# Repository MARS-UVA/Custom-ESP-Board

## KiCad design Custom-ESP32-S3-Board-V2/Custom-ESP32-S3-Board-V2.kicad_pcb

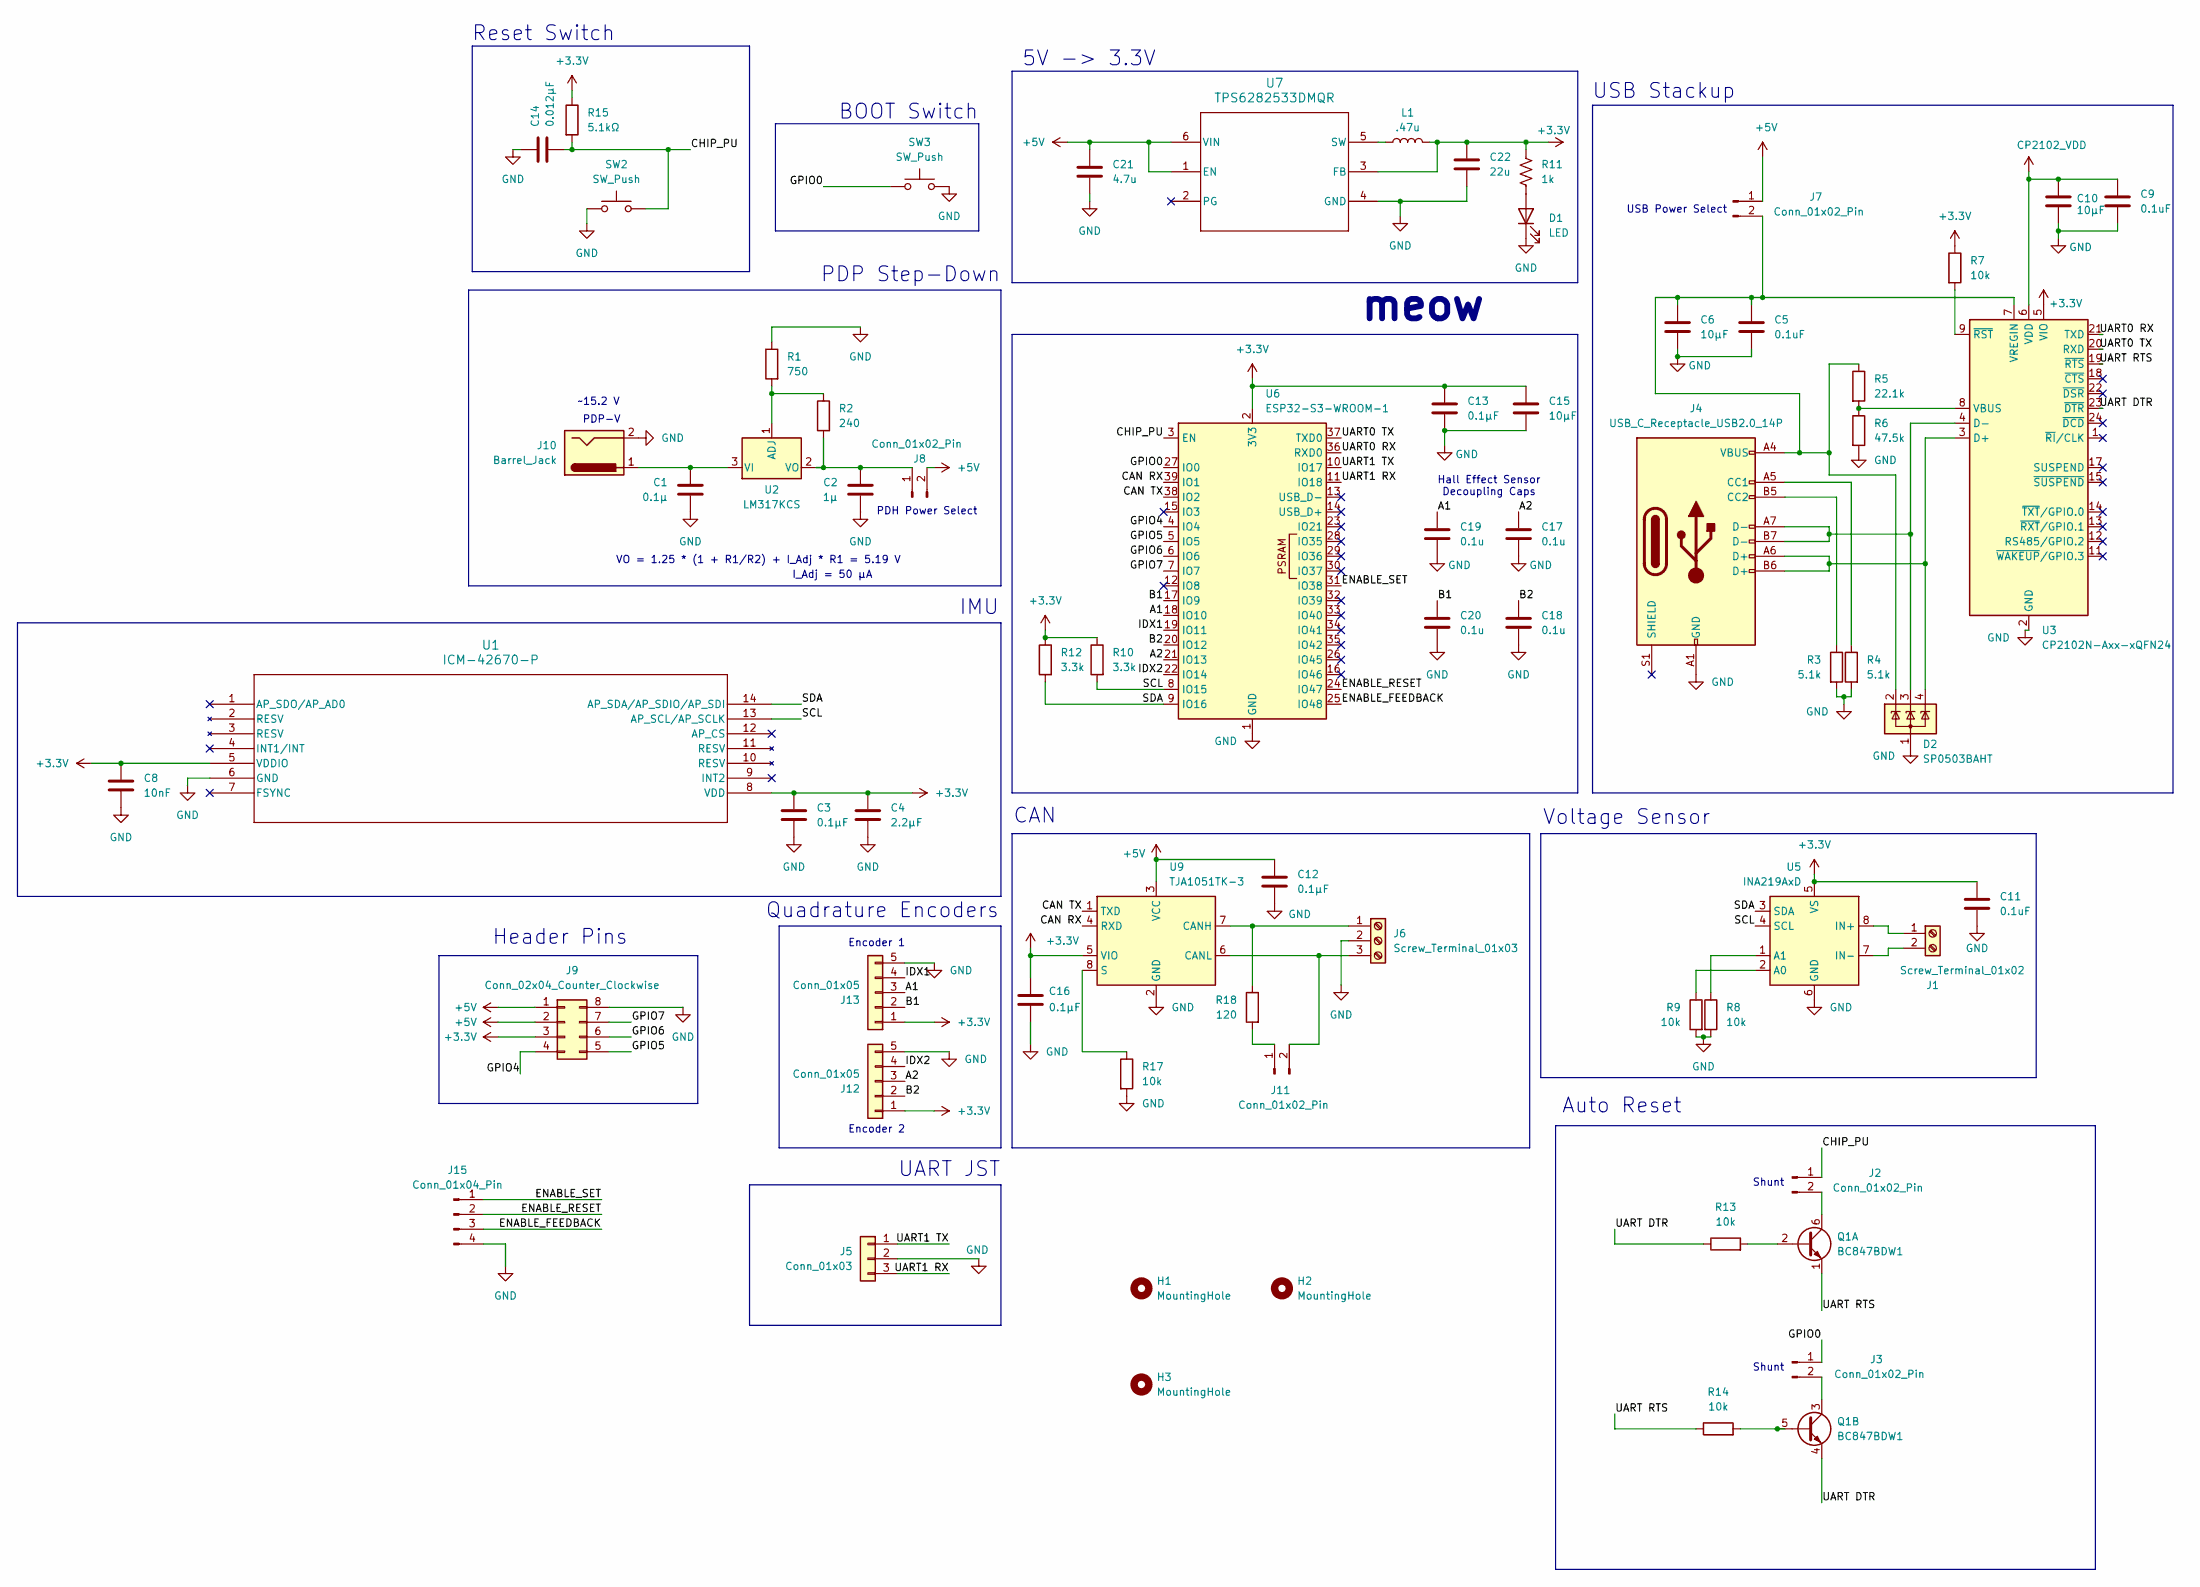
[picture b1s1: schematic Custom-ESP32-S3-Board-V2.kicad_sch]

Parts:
C1: 0.1µ; C_0402_1005Metric
C2: 1µ; C_0402_1005Metric
C3, C12, C13, C16: 0.1µF; C_0402_1005Metric
C4: 2.2µF; C_0402_1005Metric
C5, C9, C11: 0.1uF; C_0402_1005Metric
C6, C10, C15: 10µF; C_0402_1005Metric
C8: 10nF; C_0402_1005Metric
C14: 0.012µF; C_0402_1005Metric
C17, C18, C19, C20: 0.1u; C_0402_1005Metric
C21: 4.7u; C_0402_1005Metric
C22: 22u; C_0402_1005Metric
D1: LED; LED_0402_1005Metric
D2: SP0503BAHT; SOT-143
H1, H2, H3: MountingHole; MountingHole_4.5mm
J1: Screw_Terminal_01x02; TerminalBlock_Xinya_XY308-2.54-2P_1x02_P2.54mm_Horizontal
J2, J3, J7, J8, J11: Conn_01x02_Pin; PinHeader_1x02_P2.54mm_Vertical
J4: USB_C_Receptacle_USB2.0_14P; USB_C_Receptacle_HRO_TYPE-C-31-M-12
J5: Conn_01x03; JST_XH_S3B-XH-A-1_1x03_P2.50mm_Horizontal
J6: Screw_Terminal_01x03; TerminalBlock_Xinya_XY308-2.54-3P_1x03_P2.54mm_Horizontal
J9: Conn_02x04_Counter_Clockwise; PinHeader_2x04_P2.54mm_Vertical
J10: Barrel_Jack; BarrelJack_CUI_PJ-063AH_Horizontal
J12, J13: Conn_01x05; JST_XH_S5B-XH-A-1_1x05_P2.50mm_Horizontal
J15: Conn_01x04_Pin; JST_EH_B4B-EH-A_1x04_P2.50mm_Vertical
L1: .47u; L_0402_1005Metric
Q1: BC847BDW1; SOT-363_SC-70-6
R1: 750; R_0402_1005Metric
R2: 240; R_0402_1005Metric
R3, R4: 5.1k; R_0402_1005Metric
R5: 22.1k; R_0402_1005Metric
R6: 47.5k; R_0402_1005Metric
R7, R8, R9, R13, R14, R17: 10k; R_0402_1005Metric
R10, R12: 3.3k; R_0402_1005Metric
R11: 1k; R_0402_1005Metric
R15: 5.1kΩ; R_0402_1005Metric
R18: 120; R_0402_1005Metric
SW2, SW3: SW_Push; SW_SPST_PTS810
U1: ICM-42670-P; LGA14_2.5X3X0.76_IVS
U2: LM317KCS; TO-220-3_Vertical
U3: CP2102N-Axx-xQFN24; QFN-24-1EP_4x4mm_P0.5mm_EP2.6x2.6mm
U5: INA219AxD; SOIC-8_3.9x4.9mm_P1.27mm
U6: ESP32-S3-WROOM-1
U7: TPS6282533DMQR
U9: TJA1051TK-3; HVSON-8-1EP_3x3mm_P0.65mm_EP1.6x2.4mm

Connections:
+3.3V: C3.1, C4.1, C8.1, C11.1, C13.1, C15.1, C16.1, C22.1, J9.3, J12.1, J13.1, L1.2, R7.1, R10.1, R11.1, R12.1, R15.1, U1.5 (VDDIO), U1.8 (VDD), U3.5 (VIO), U5.5 (VS), U6.2 (3V3), U7.3 (FB), U9.5 (VIO)
+5V: C12.1, C21.1, J7.1, J8.2, J9.1, J9.2, U7.1 (EN), U7.6 (VIN), U9.3 (VCC)
/A1: C19.1, J13.3, U6.18 (IO10)
/A2: C17.1, J12.3, U6.21 (IO13)
/B1: C20.1, J13.2, U6.17 (IO9)
/B2: C18.1, J12.2, U6.20 (IO12)
/CAN RX: U6.39 (IO1), U9.4 (RXD)
/CAN TX: U6.38 (IO2), U9.1 (TXD)
/CHIP_PU: C14.2, J2.1, R15.2, SW2.2, U6.3 (EN)
/ENABLE_FEEDBACK: J15.3, U6.25 (IO48)
/ENABLE_RESET: J15.2, U6.24 (IO47)
/ENABLE_SET: J15.1, U6.31 (IO38)
/GPIO0: J3.1, SW3.2, U6.27 (IO0)
/GPIO4: J9.4, U6.4 (IO4)
/GPIO5: J9.5, U6.5 (IO5)
/GPIO6: J9.6, U6.6 (IO6)
/GPIO7: J9.7, U6.7 (IO7)
/IDX1: J13.4, U6.19 (IO11)
/IDX2: J12.4, U6.22 (IO14)
/SCL: R10.2, U1.13 (AP_SCL/AP_SCLK), U5.4 (SCL), U6.8 (IO15)
/SDA: R12.2, U1.14 (AP_SDA/AP_SDIO/AP_SDI), U5.3 (SDA), U6.9 (IO16)
/UART0 RX: U3.21 (TXD), U6.36 (RXD0)
/UART0 TX: U3.20 (RXD), U6.37 (TXD0)
/UART1 RX: J5.3, U6.11 (IO18)
/UART1 TX: J5.1, U6.10 (IO17)
/UART DTR: Q1.4 (E2), R13.1, U3.23 (~DTR)
/UART RTS: Q1.1 (E1), R14.1, U3.19 (~RTS)
CP2102_VDD: C9.1, C10.1, U3.6 (VDD)
GND: C1.2, C2.2, C3.2, C4.2, C5.2, C6.2, C8.2, C9.2, C10.2, C11.2, C12.2, C13.2, C14.1, C15.2, C16.2, C17.2, C18.2, C19.2, C20.2, C21.2, C22.2, D1.1 (K), D2.1 (A), J4.A1 (GND), J4.A12 (GND), J4.B1 (GND), J4.B12 (GND), J5.2, J6.2, J9.8, J10.2, J12.5, J13.5, J15.4, R1.1, R3.2, R4.2, R6.2, R8.2, R9.2, R17.2, SW2.1, SW3.1, U1.6 (GND), U3.2 (GND), U3.25 (GND), U5.6 (GND), U6.1 (GND), U6.40 (GND), U6.41 (GND), U7.4 (GND), U9.2 (GND), U9.9 (GND)
unnamed: D1.2 (A), R11.2
unnamed: J1.1, U5.8 (IN+)
unnamed: J1.2, U5.7 (IN-)
unnamed: J2.2, Q1.6 (C1)
unnamed: J3.2, Q1.3 (C2)
unnamed: J4.A5 (CC1), R4.1
unnamed: J4.B5 (CC2), R3.1
unnamed: J6.1, R18.1, U9.7 (CANH)
unnamed: C5.1, C6.1, D2.2 (K), J4.A4 (VBUS), J4.A9 (VBUS), J4.B4 (VBUS), J4.B9 (VBUS), J7.2, R5.1, U3.7 (VREGIN)
unnamed: C2.1, J8.1, R2.2, U2.2 (VO)
unnamed: J11.1, R18.2
unnamed: J6.3, J11.2, U9.6 (CANL)
unnamed: Q1.2 (B1), R13.2
unnamed: Q1.5 (B2), R14.2
unnamed: R1.2, R2.1, U2.1 (ADJ)
unnamed: C1.1, J10.1, U2.3 (VI)
unnamed: D2.4 (K), J4.A6 (D+), J4.B6 (D+), U3.3 (D+)
unnamed: D2.3 (K), J4.A7 (D-), J4.B7 (D-), U3.4 (D-)
unnamed: R5.2, R6.1, U3.8 (VBUS)
unnamed: R7.2, U3.9 (~RST)
unnamed: R9.1, U5.2 (A0)
unnamed: R8.1, U5.1 (A1)
unnamed: L1.1, U7.5 (SW)
unnamed: R17.1, U9.8 (S)

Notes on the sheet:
Encoder 1
VO = 1.25 * (1 + R1/R2) + I_Adj * R1 = 5.19 V
5V -> 3.3V
Reset Switch
Shunt
UART JST
Encoder 2
Quadrature Encoders
~15.2 V
USB Power Select
IMU
I_Adj = 50 µA
Auto Reset
Hall Effect Sensor Decoupling Caps
meow
CAN
PDP-V
Header Pins
PDH Power Select
BOOT Switch
USB Stackup
Voltage Sensor
PDP Step-Down

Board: 4 copper layers, 68 parts (0 on the bottom side), 53 nets, no tracks yet.

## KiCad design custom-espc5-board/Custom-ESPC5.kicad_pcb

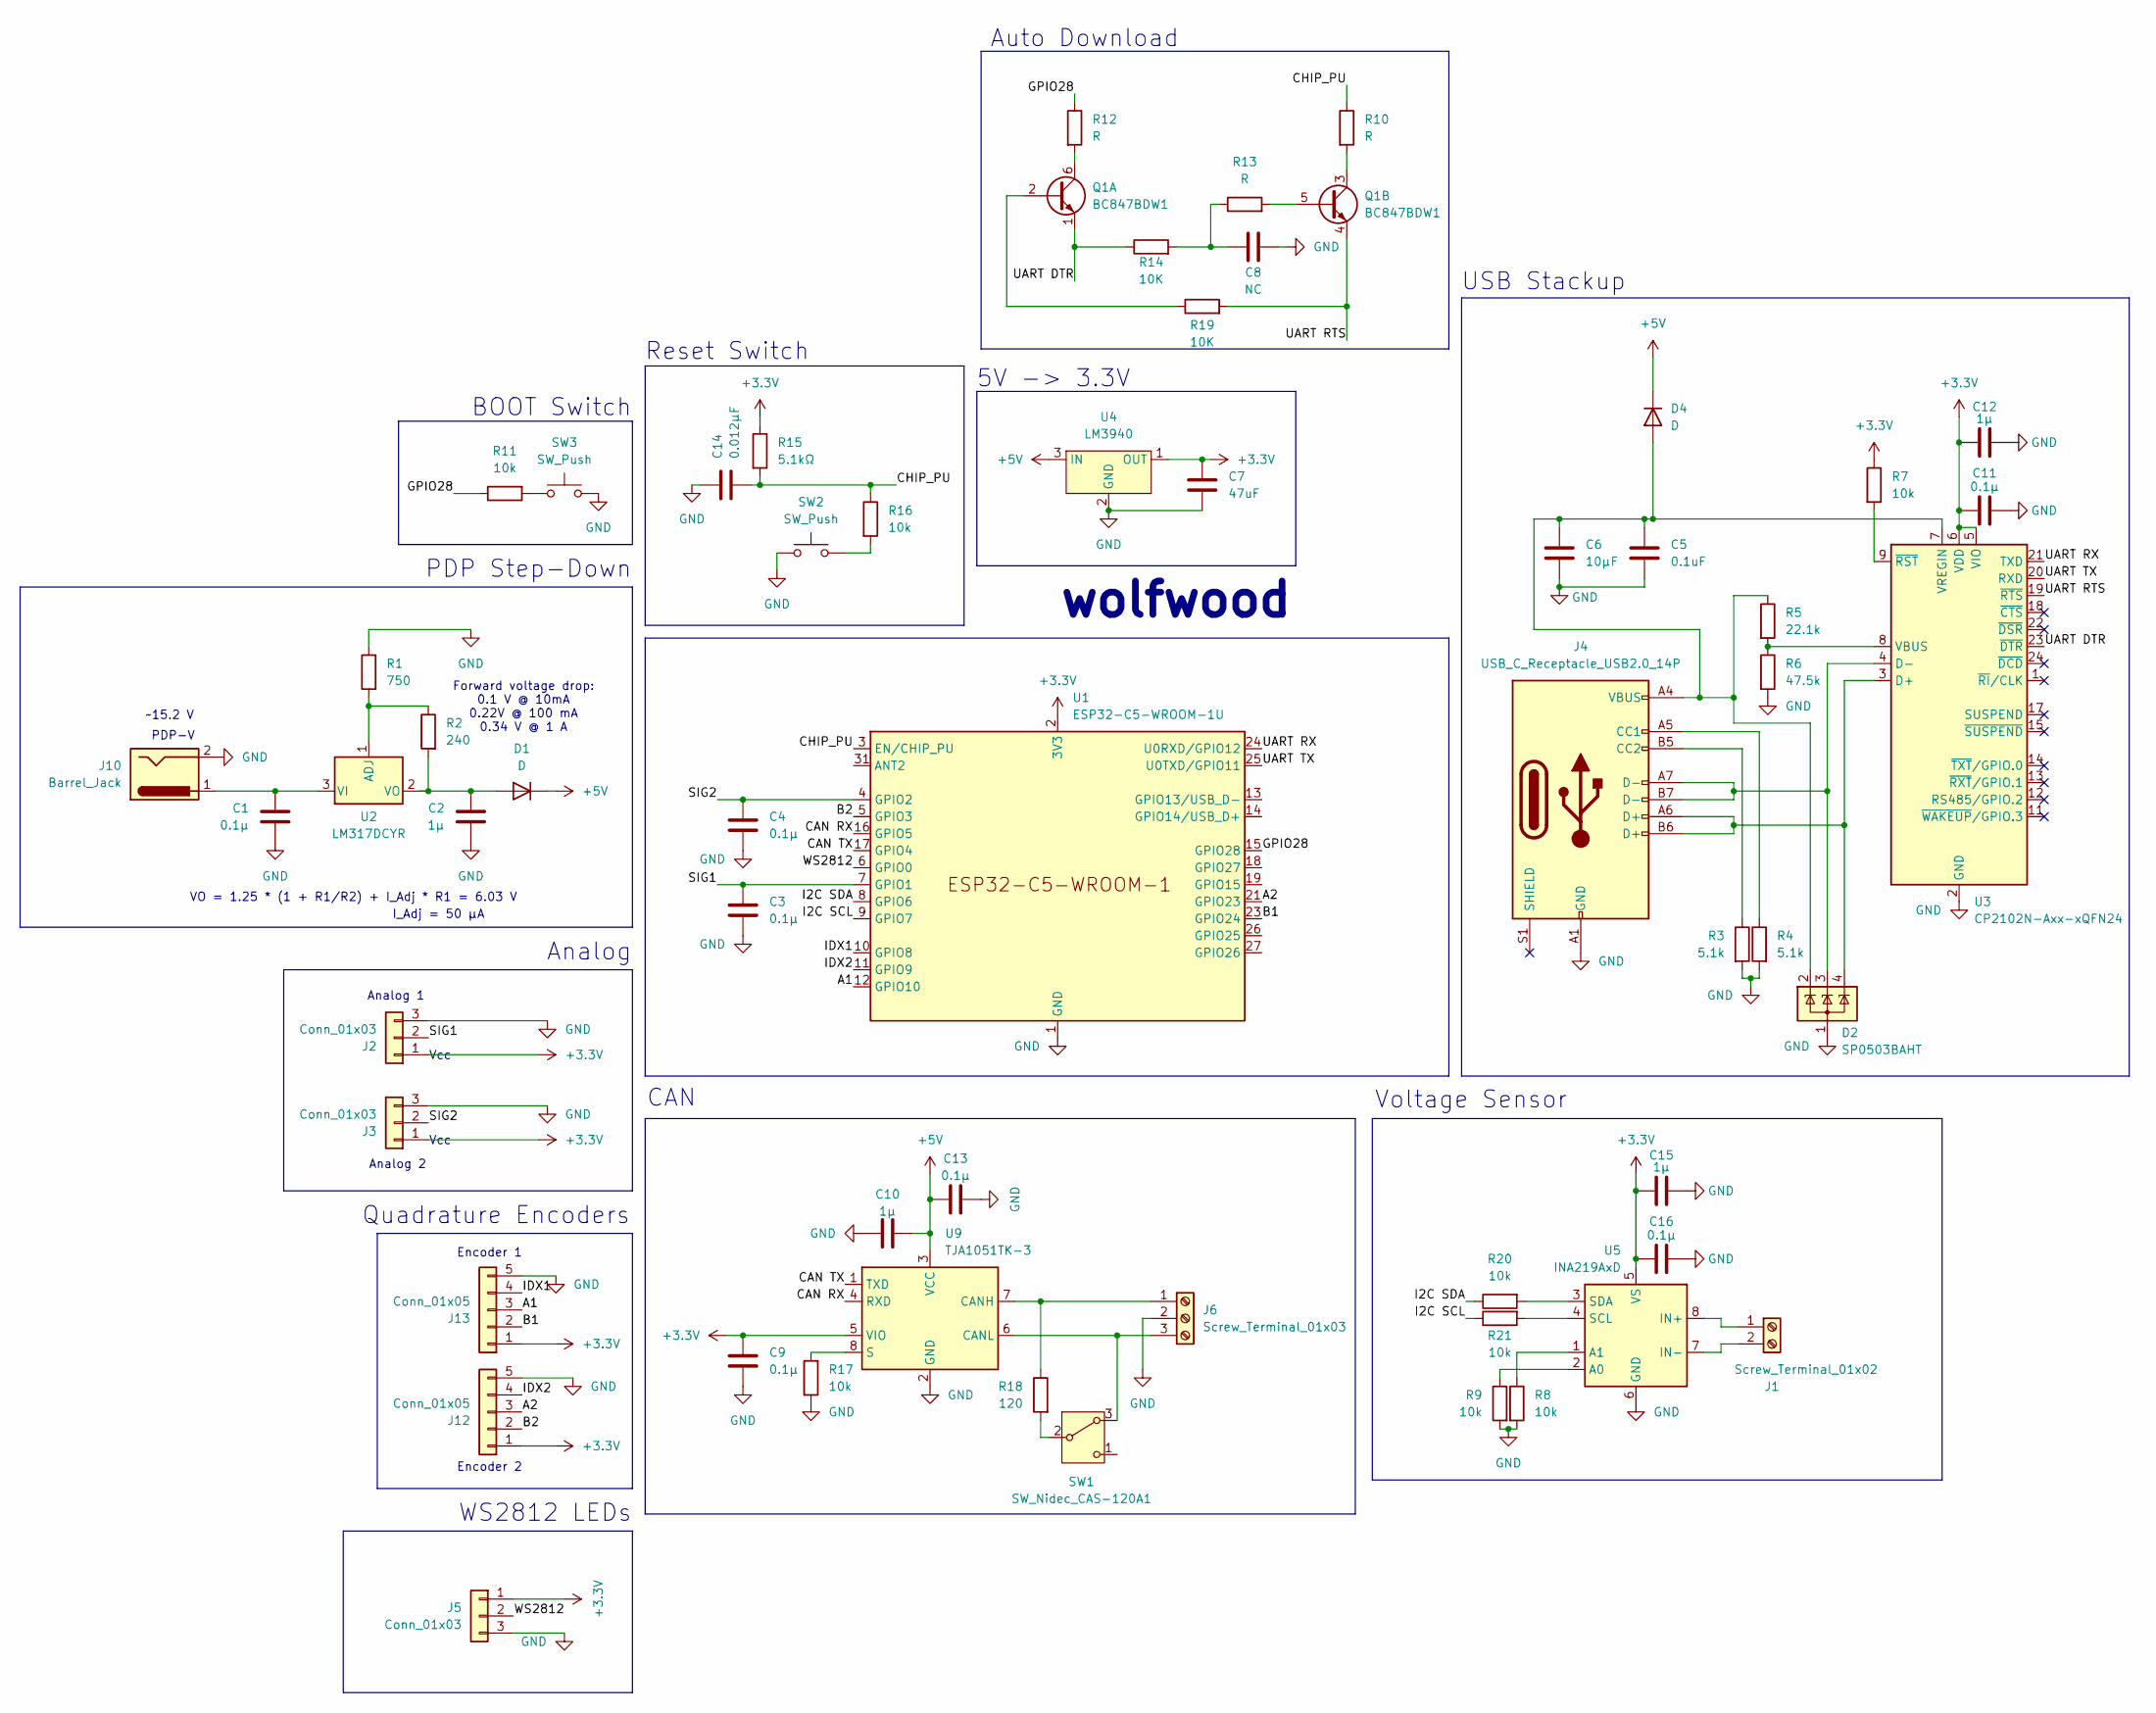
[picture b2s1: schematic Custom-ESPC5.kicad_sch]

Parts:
C1, C3, C4, C9, C11, C13, C16: 0.1µ; C_0402_1005Metric
C2, C10, C12, C15: 1µ; C_0402_1005Metric
C5: 0.1uF; C_0402_1005Metric
C6: 10µF; C_0402_1005Metric
C7: 47uF; C_0402_1005Metric
C8: NC; C_0402_1005Metric
C14: 0.012µF; C_0402_1005Metric
D1, D4: D; USC-TOS
D2: SP0503BAHT; SOT-143
J1: Screw_Terminal_01x02; TerminalBlock_Xinya_XY308-2.54-2P_1x02_P2.54mm_Horizontal
J2, J3, J5: Conn_01x03; JST_XH_S3B-XH-A-1_1x03_P2.50mm_Horizontal
J4: USB_C_Receptacle_USB2.0_14P; USB_C_Receptacle_HRO_TYPE-C-31-M-12
J6: Screw_Terminal_01x03; TerminalBlock_Xinya_XY308-2.54-3P_1x03_P2.54mm_Horizontal
J10: Barrel_Jack; BarrelJack_CUI_PJ-063AH_Horizontal
J12, J13: Conn_01x05; JST_XH_S5B-XH-A-1_1x05_P2.50mm_Horizontal
Q1: BC847BDW1; SOT-363_SC-70-6
R1: 750; R_0402_1005Metric
R2: 240; R_0402_1005Metric
R3, R4: 5.1k; R_0402_1005Metric
R5: 22.1k; R_0402_1005Metric
R6: 47.5k; R_0402_1005Metric
R7, R8, R9, R11, R16, R17, R20, R21: 10k; R_0402_1005Metric
R10, R12, R13: R; R_0402_1005Metric
R14, R19: 10K; R_0402_1005Metric
R15: 5.1kΩ; R_0402_1005Metric
R18: 120; R_0402_1005Metric
SW1: SW_Nidec_CAS-120A1; Nidec_Copal_CAS-120A
SW2, SW3: SW_Push; SW_SPST_PTS810
U1: ESP32-C5-WROOM-1U
U2: LM317DCYR; SOT-223-3_TabPin2
U3: CP2102N-Axx-xQFN24; QFN-24-1EP_4x4mm_P0.5mm_EP2.6x2.6mm
U4: LM3940; SOT-223-3_TabPin2
U5: INA219AxD; SOIC-8_3.9x4.9mm_P1.27mm
U9: TJA1051TK-3; HVSON-8-1EP_3x3mm_P0.65mm_EP1.6x2.4mm

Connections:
+3.3V: C7.1, C9.2, C11.2, C12.2, C15.2, C16.2, J2.1, J3.1, J5.1, J12.1, J13.1, R7.1, R15.1, U1.2 (3V3), U3.5 (VIO), U3.6 (VDD), U4.1 (OUT), U5.5 (VS), U9.5 (VIO)
+5V: C10.2, C13.2, D1.1 (K), D4.1 (K), U4.3 (IN), U9.3 (VCC)
/A1: J13.3, U1.12 (GPIO10)
/A2: J12.3, U1.21 (GPIO23)
/B1: J13.2, U1.23 (GPIO24)
/B2: J12.2, U1.5 (GPIO3)
/CAN RX: U1.16 (GPIO5), U9.4 (RXD)
/CAN TX: U1.17 (GPIO4), U9.1 (TXD)
/CHIP_PU: C14.2, R10.1, R15.2, R16.1, U1.3 (EN/CHIP_PU)
/GPIO28: R11.1, R12.1, U1.15 (GPIO28)
/I2C SCL: R21.1, U1.9 (GPIO7)
/I2C SDA: R20.1, U1.8 (GPIO6)
/IDX1: J13.4, U1.10 (GPIO8)
/IDX2: J12.4, U1.11 (GPIO9)
/SIG1: C3.1, J2.2, U1.7 (GPIO1)
/SIG2: C4.1, J3.2, U1.4 (GPIO2)
/UART DTR: Q1.1 (E1), R14.1, U3.23 (~DTR)
/UART RTS: Q1.4 (E2), R19.2, U3.19 (~RTS)
/UART RX: U1.24 (U0RXD/GPIO12), U3.21 (TXD)
/UART TX: U1.25 (U0TXD/GPIO11), U3.20 (RXD)
/WS2812: J5.2, U1.6 (GPIO0)
GND: C1.2, C2.2, C3.2, C4.2, C5.2, C6.2, C7.2, C8.2, C9.1, C10.1, C11.1, C12.1, C13.1, C14.1, C15.1, C16.1, D2.1 (A), J2.3, J3.3, J4.A1 (GND), J4.A12 (GND), J4.B1 (GND), J4.B12 (GND), J5.3, J6.2, J10.2, J12.5, J13.5, R1.1, R3.2, R4.2, R6.2, R8.2, R9.2, R17.2, SW2.1, SW3.1, U1.1 (GND), U1.28 (GND), U1.29 (GND), U1.30 (GND), U1.32 (GND), U3.2 (GND), U3.25 (GND), U4.2 (GND), U5.6 (GND), U9.2 (GND), U9.9 (GND)
unnamed: C8.1, R13.1, R14.2
unnamed: C2.1, D1.2 (A), R2.2, U2.2 (VO)
unnamed: C5.1, C6.1, D2.2 (K), D4.2 (A), J4.A4 (VBUS), J4.A9 (VBUS), J4.B4 (VBUS), J4.B9 (VBUS), R5.1, U3.7 (VREGIN)
unnamed: J1.1, U5.8 (IN+)
unnamed: J1.2, U5.7 (IN-)
unnamed: J4.A5 (CC1), R4.1
unnamed: J4.B5 (CC2), R3.1
unnamed: J6.1, R18.1, U9.7 (CANH)
unnamed: J6.3, SW1.3 (A), U9.6 (CANL)
unnamed: Q1.2 (B1), R19.1
unnamed: Q1.6 (C1), R12.2
unnamed: Q1.5 (B2), R13.2
unnamed: Q1.3 (C2), R10.2
unnamed: R11.2, SW3.2
unnamed: R16.2, SW2.2
unnamed: R18.2, SW1.2 (B)
unnamed: R1.2, R2.1, U2.1 (ADJ)
unnamed: C1.1, J10.1, U2.3 (VI)
unnamed: D2.4 (K), J4.A6 (D+), J4.B6 (D+), U3.3 (D+)
unnamed: D2.3 (K), J4.A7 (D-), J4.B7 (D-), U3.4 (D-)
unnamed: R5.2, R6.1, U3.8 (VBUS)
unnamed: R7.2, U3.9 (~RST)
unnamed: R9.1, U5.2 (A0)
unnamed: R8.1, U5.1 (A1)
unnamed: R21.2, U5.4 (SCL)
unnamed: R20.2, U5.3 (SDA)
unnamed: R17.1, U9.8 (S)

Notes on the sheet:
Quadrature Encoders
Encoder 1
USB Stackup
WS2812 LEDs
CAN
Auto Download
BOOT Switch
VO = 1.25 * (1 + R1/R2) + I_Adj * R1 = 6.03 V
Forward voltage drop: 0.1 V @ 10mA 0.22V @ 100 mA 0.34 V @ 1 A
Vcc
Analog
I_Adj = 50 µA
Analog 1
Reset Switch
PDP Step-Down
Voltage Sensor
~15.2 V
wolfwood
Analog 2
Encoder 2
PDP-V
5V -> 3.3V

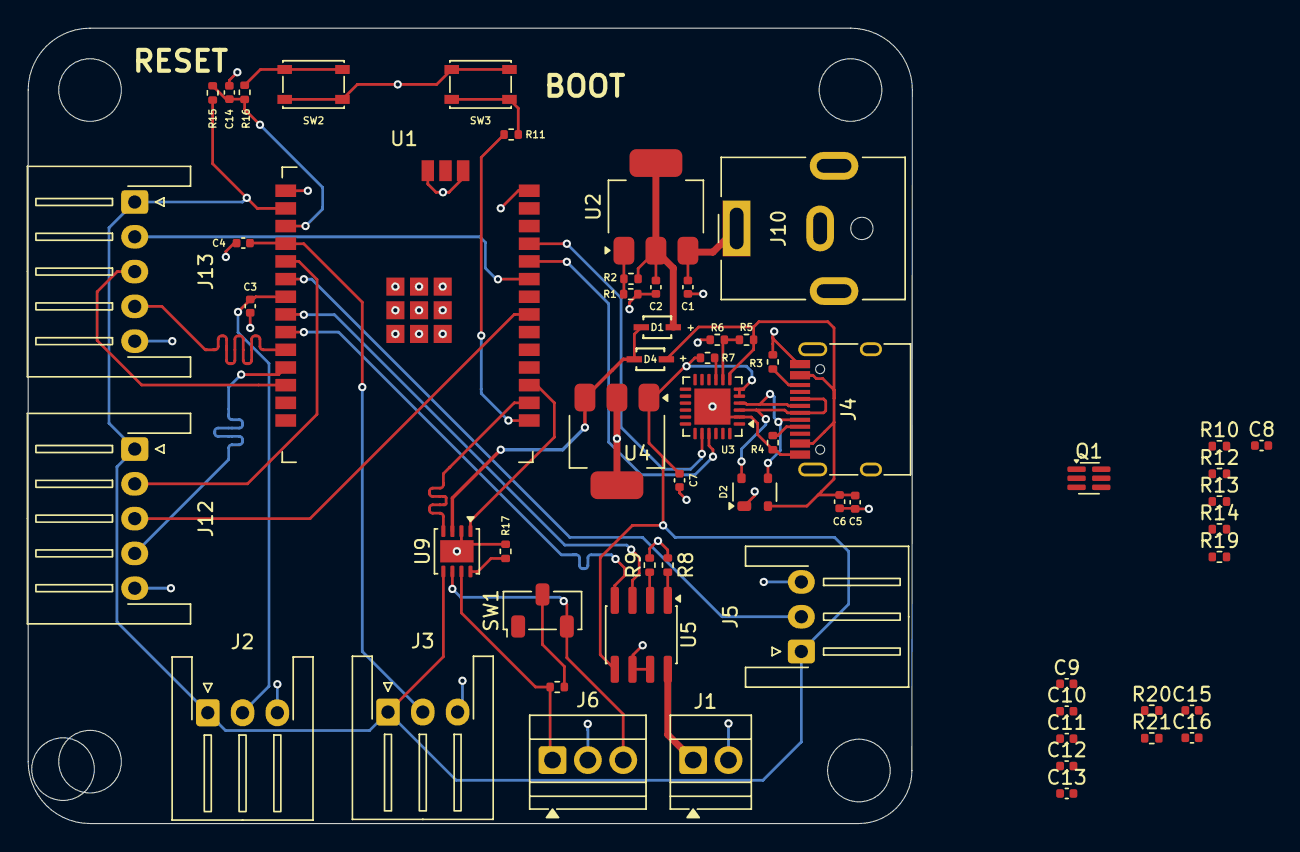
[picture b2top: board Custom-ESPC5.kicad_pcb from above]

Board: 4 copper layers, 63.5 x 57.1 mm, 59 parts (0 on the bottom side), 49 nets.

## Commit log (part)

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2026-02-20 Create blank project
2026-02-22 finish schem, start board work
2026-02-22 closed kicad
2026-02-22 aa
    fitting things into board dimensions
2026-02-23 board layout
2026-02-23 Finish preliminary board tracings (NOT COMPLETE)
2026-02-24 finish base
2026-02-24 custom board preliminary complete
2026-02-24 Increase density
2026-02-24 fix name
2026-03-11 fix some silkscreens, get rounded corners
2026-03-11 Update Custom-ESPC5.kicad_sch
    Made correction to lm317 circuit annotations
2026-03-12 Update Custom-ESPC5.kicad_sch
    Added datasheet link
2026-03-13 fixed schematic changes
    fixed schematic changes like master austin said
2026-03-15 Fix layout file formatting
2026-03-15 Update schematic
    Fix I2C pull-up resistors
2026-04-03 s3 devboard + imu
    austin yun
2026-04-05 Add bypass caps
2026-04-05 Changed voltage regulator footprints and schematic
2026-04-10 renamed folders
2026-04-10 Update layout
    apply schematic changes to layout
2026-04-17 add auto-reset
2026-04-17 Finalize Schematic
2026-04-17 Fix pin labels in schematic
2026-04-17 Place components for layout
2026-04-17 Finish routing for subcircuits
2026-04-18 finished pcb design, left mounting hole still chopped
    austin yun 😝😝😝😝😝😝
2026-04-18 Fix board outline
2026-04-19 did some silkscreen labeling
2026-04-21 more labeling
2026-04-21 Final Edits
    Generated gerbers
2026-04-22 Edit silkscreen
    Increased package size of C7 :(
2026-04-23 Generate new gerbers
